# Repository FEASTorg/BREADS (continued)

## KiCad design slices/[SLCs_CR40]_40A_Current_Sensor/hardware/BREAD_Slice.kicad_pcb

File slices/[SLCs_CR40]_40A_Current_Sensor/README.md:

# Broadly Reconfigurable and Expandable Automation Device (BREAD) -- Slice Datasheet: 4**0A Current Sensor Slice** (SLC-CR40)

By: Nicholas Whisman (ngwhisma@mtu.edu) -- Revision 0, on

## Short Device Description

This slice acts as a current sensor, and is rated for up to ±40 Amps.
The sensor outputs a voltage signal linearly related to the current
flowing through the chip, at an approximate resolution of 50 mV / Amp.

## Quick Information

Device at a Glance

  --------------------- ---------------------------------
  Short title           40A Current Detector
  Part \#               SLC-CR40
  Repository Link       Link to OSF or other repository
  Academic Paper DOI    DOI link to published paper
  Device Cost           Monetary cost of the device
  Assembly Difficulty   Medium. Millable.
  Application Area      Power Analysis, Controls
  --------------------- ---------------------------------

Device Connections

Current Input Screw Terminals

  -------- -------------------------------------------------------------------------------------- --------
  Pin \#   Description                                                                            Rating
  J2       Sizeable blade connector for current channel throughput. Positive lead on the right.   50A+
  J3       Sizeable blade connector for current channel throughput. Positive lead on the right.   50A+
  J4       Sizeable blade connector for current channel throughput. Positive lead on the right.   50A+
  J5       Sizeable blade connector for current channel throughput. Positive lead on the right.   50A+
  J6       Sizeable blade connector for current channel throughput. Positive lead on the right.   50A+
  J7       Sizeable blade connector for current channel throughput. Positive lead on the right.   50A+
  J8       Sizeable blade connector for current channel throughput. Positive lead on the right.   50A+
  J9       Sizeable blade connector for current channel throughput. Positive lead on the right.   50A+
  -------- -------------------------------------------------------------------------------------- --------

## Commands

  --------------------------------------------------------------------- ------------ ------------------------ ----------------------------
  **Setup **(no significant returns)                                                                          
  **Byte**: Address                                                     **Bit**: 1   **Float: **Target Temp   **Float: **Ramp Rate (d/m)
  **Read Current **(returns the current through the selected channel)                                         
  **Byte**: Address                                                     **Bit**: 0   **Float: **0             **Float: **0
  --------------------------------------------------------------------- ------------ ------------------------ ----------------------------

## Schematic

![Figure 1: BREAD Connection Pins + Power
Capacitors](Pictures/10000201000000AB0000008BB51D58A998ECB56B.png "fig:"){width="1.7811in"
height="1.448in"}\
\
\
\
\
\
\
\
\
\
![Figure 2: Arduino
Nano](Pictures/10000201000000B4000000F5D2FAF377839CEBA3.png "fig:"){width="1.8752in"
height="2.552in"}\
\

![Figure 3: One of four identical current sensing
channels](Pictures/10000201000000F900000074C687B7F5A6EA3E1E.png "fig:"){width="2.5937in"
height="1.2083in"}

\
\
\
\
\
\

## Bill of Materials

  ------------ -------------------------------- ---------- ------------- -----------------------------------------------------------------------------------------------------------------------------------------------------------------
  Designator   Description                      Quantity   Cost / part   URL
  U1-4         40A Current Sensor Chip          4          5.68          <https://www.digikey.com/en/products/detail/allegro-microsystems/ACS723KMATR-40AB-T/5225380>
  J2-J9        Blade Connectors                 8          0.37          [https://www.digikey.com/en/products/detail/w%C3%BCrth-elektronik/7474966/9488016](https://www.digikey.com/en/products/detail/würth-elektronik/7474966/9488016)
  C1-2         1206 Packaging 10 µF Capacitor   2          0.64          <https://www.digikey.com/short/qfrbqfhd>
  A1           Arduino Nano                     1          22.00         <https://www.digikey.com/en/products/detail/arduino/A000005/2638989>
  J1           01x10 Female Header Pins         1          0.79          <https://www.digikey.com/short/23bfwwjh>
  ------------ -------------------------------- ---------- ------------- -----------------------------------------------------------------------------------------------------------------------------------------------------------------

## Construction & Fabrication

List any tools that are required and short guide on the order which
parts should be soldered / assembled. Be sure to note any specialized
methods and point out components that may easily be soldered in the
incorrect orientation. Additionally include at least one picture of the
assembled board (include both sides if there are components on both
sides).

\[Image of the assembled Circuit Board\]

Fig #. Subtitle should go here.

## Configuration & Calibration

Include a list of default jumper and potentiometer positions:

Hardware Positions

-   Turn P1 to be roughly 50%
-   Turn P2 to be completely closed (turn clockwise until potentiometer
    clicks)
-   Place a jumper to short out J3. Etc...

Detail any key parameters the end-user may want to adjust in the
firmware, and if there are any special instructions before programming
the Slice.

Tools Required For Calibration

-   An oscilloscope with at least 15Mhz sampling
-   A multimeter. Etc...

List all of the tools / instruments required for calibration. Provide a
detailed & step by step guide on how to calibrate (or validate) each
unique type of channel on the card. Include what variables in the
firmware may need to be adjusted (and when). Attach a wiring diagram for
each relevant calibration circuit.

\[Image of the calibration circuit\]

Fig #. Subtitle should go here.

## Usage & Constraints

List the relevant constraints for each type of channel on the card.
These parameters may be quantities like max current, max voltage,
frequency, sampling frequency, etc.

List an example wiring diagram of the slice in use, as well as some
suggested applications

\[Image of the example usage wiring diagram\]

Fig #. Subtitle should go here.

## General Comments on Slice

This section is intended as a catch-all for any topics that are relevant
to the Slice that don't fit in any other category.

## Revision Notes

-   Rev 0 -- Initial document release (DATE HERE)

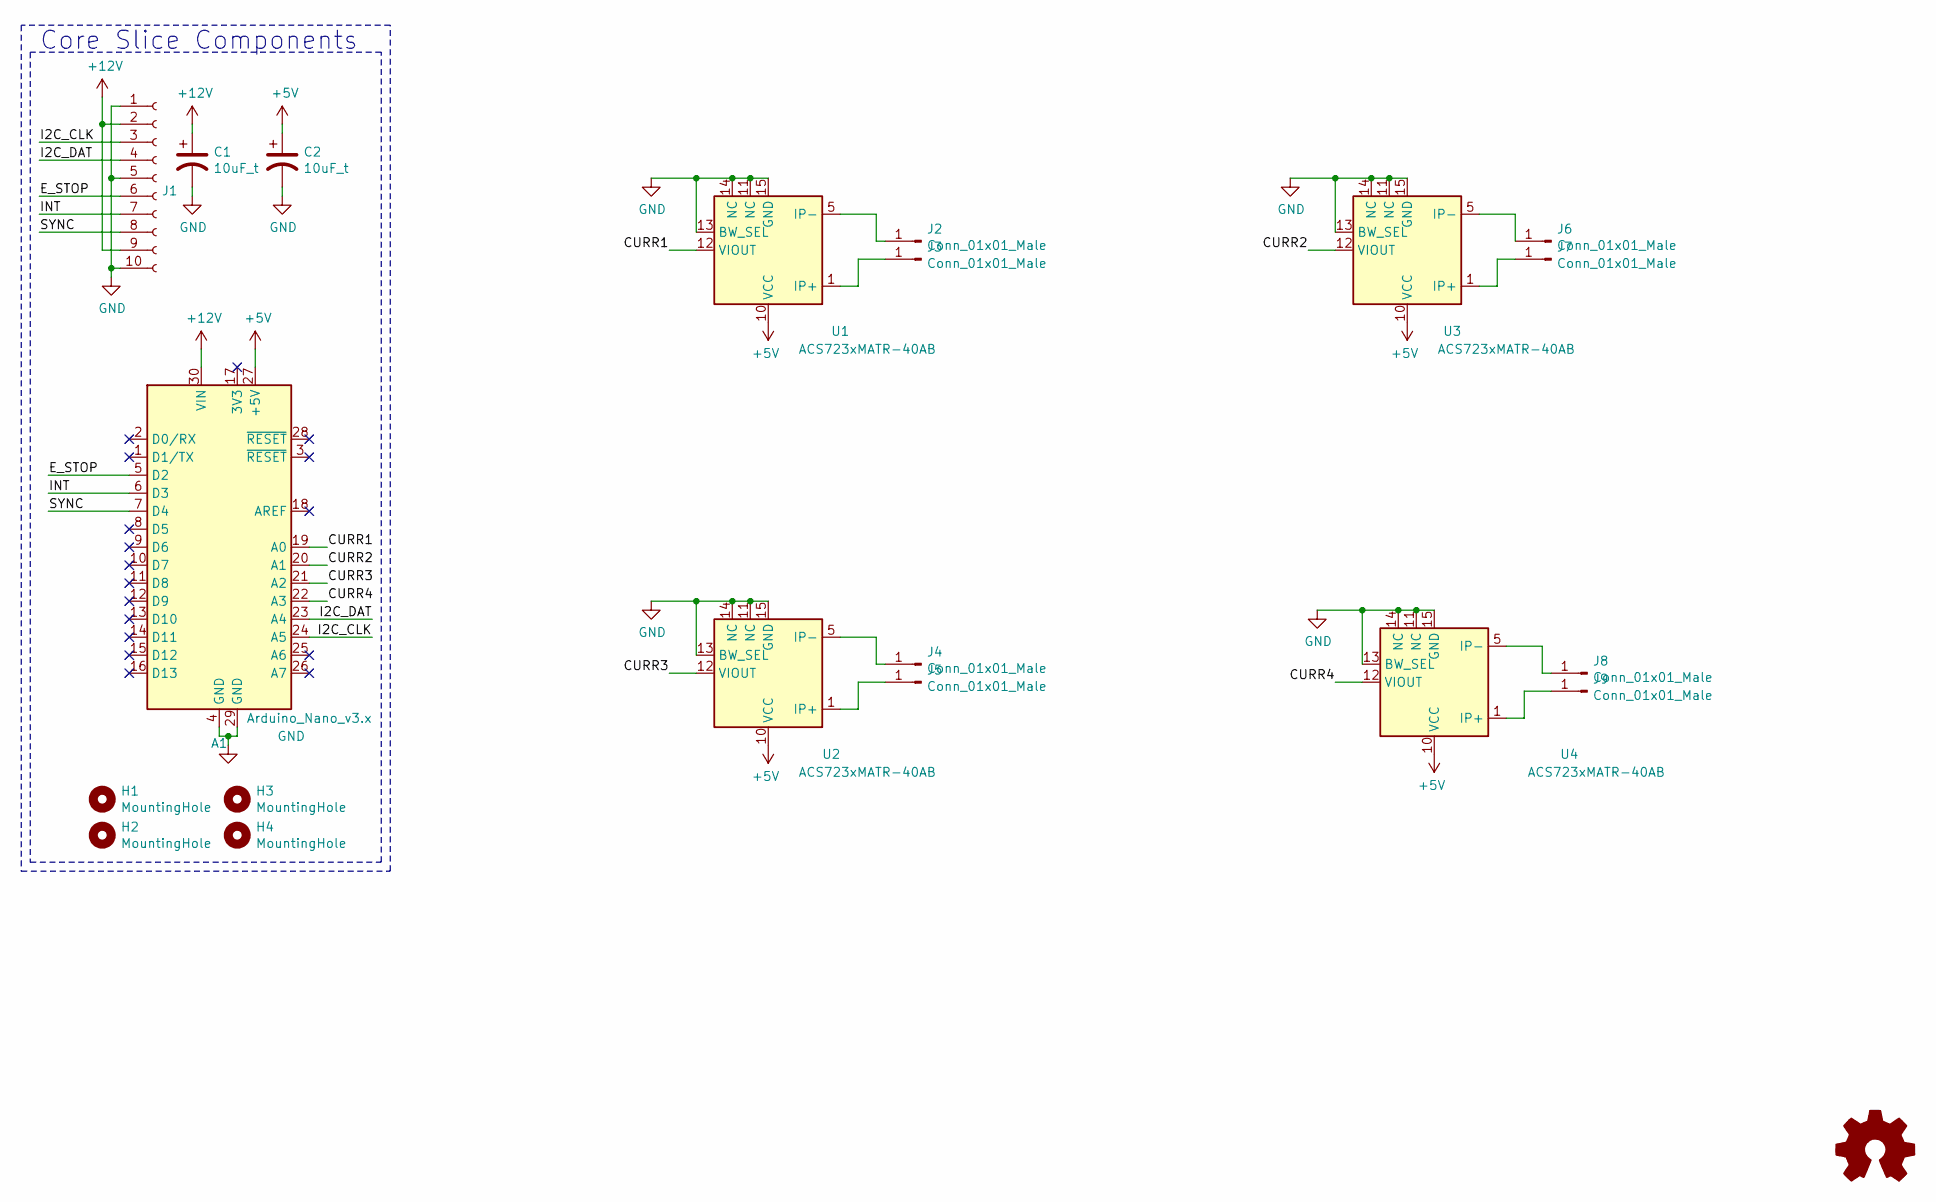
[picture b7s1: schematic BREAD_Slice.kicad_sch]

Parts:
A1: Arduino_Nano_v3.x; Arduino_Nano
C1, C2: 10uF_t; C_2312; Part # T491C106K025AT
H1, H2, H3, H4: MountingHole; MountingHole_3.2mm_M3_DIN965_Pad
J1: Conn_01x10_Female; PinSocket_1x10_P2.54mm_Horizontal
J2, J3, J4, J5, J6, J7, J8, J9: Conn_01x01_Male; Blade_Connector
Logo1: Logo_Open_Hardware_Small; OSHW-Symbol_6.7x6mm_SilkScreen
U1, U2, U3, U4: ACS723xMATR-40AB; SOIC-16W_7.5x10.3mm_P1.27mm

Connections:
+5V: A1.27 (+5V), C2.1, U1.10 (VCC), U2.10 (VCC), U3.10 (VCC), U4.10 (VCC)
+12V: A1.30 (VIN), C1.1, J1.2, J1.9
/CURR1: A1.19 (A0), U1.12 (VIOUT)
/CURR2: A1.20 (A1), U3.12 (VIOUT)
/CURR3: A1.21 (A2), U2.12 (VIOUT)
/CURR4: A1.22 (A3), U4.12 (VIOUT)
/E_STOP: A1.5 (D2), J1.6
/I2C_CLK: A1.24 (A5), J1.3
/I2C_DAT: A1.23 (A4), J1.4
/INT: A1.6 (D3), J1.7
/SYNC: A1.7 (D4), J1.8
GND: A1.4 (GND), A1.29 (GND), C1.2, C2.2, J1.1, J1.5, J1.10, U1.11 (NC), U1.13 (BW_SEL), U1.14 (NC), U1.15 (GND), U2.11 (NC), U2.13 (BW_SEL), U2.14 (NC), U2.15 (GND), U3.11 (NC), U3.13 (BW_SEL), U3.14 (NC), U3.15 (GND), U4.11 (NC), U4.13 (BW_SEL), U4.14 (NC), U4.15 (GND)
unnamed: J2.1, U1.5 (IP-), U1.6 (IP-), U1.7 (IP-), U1.8 (IP-)
unnamed: J3.1, U1.1 (IP+), U1.2 (IP+), U1.3 (IP+), U1.4 (IP+)
unnamed: J4.1, U2.5 (IP-), U2.6 (IP-), U2.7 (IP-), U2.8 (IP-)
unnamed: J5.1, U2.1 (IP+), U2.2 (IP+), U2.3 (IP+), U2.4 (IP+)
unnamed: J6.1, U3.5 (IP-), U3.6 (IP-), U3.7 (IP-), U3.8 (IP-)
unnamed: J7.1, U3.1 (IP+), U3.2 (IP+), U3.3 (IP+), U3.4 (IP+)
unnamed: J8.1, U4.5 (IP-), U4.6 (IP-), U4.7 (IP-), U4.8 (IP-)
unnamed: J9.1, U4.1 (IP+), U4.2 (IP+), U4.3 (IP+), U4.4 (IP+)

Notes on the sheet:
Core Slice Components

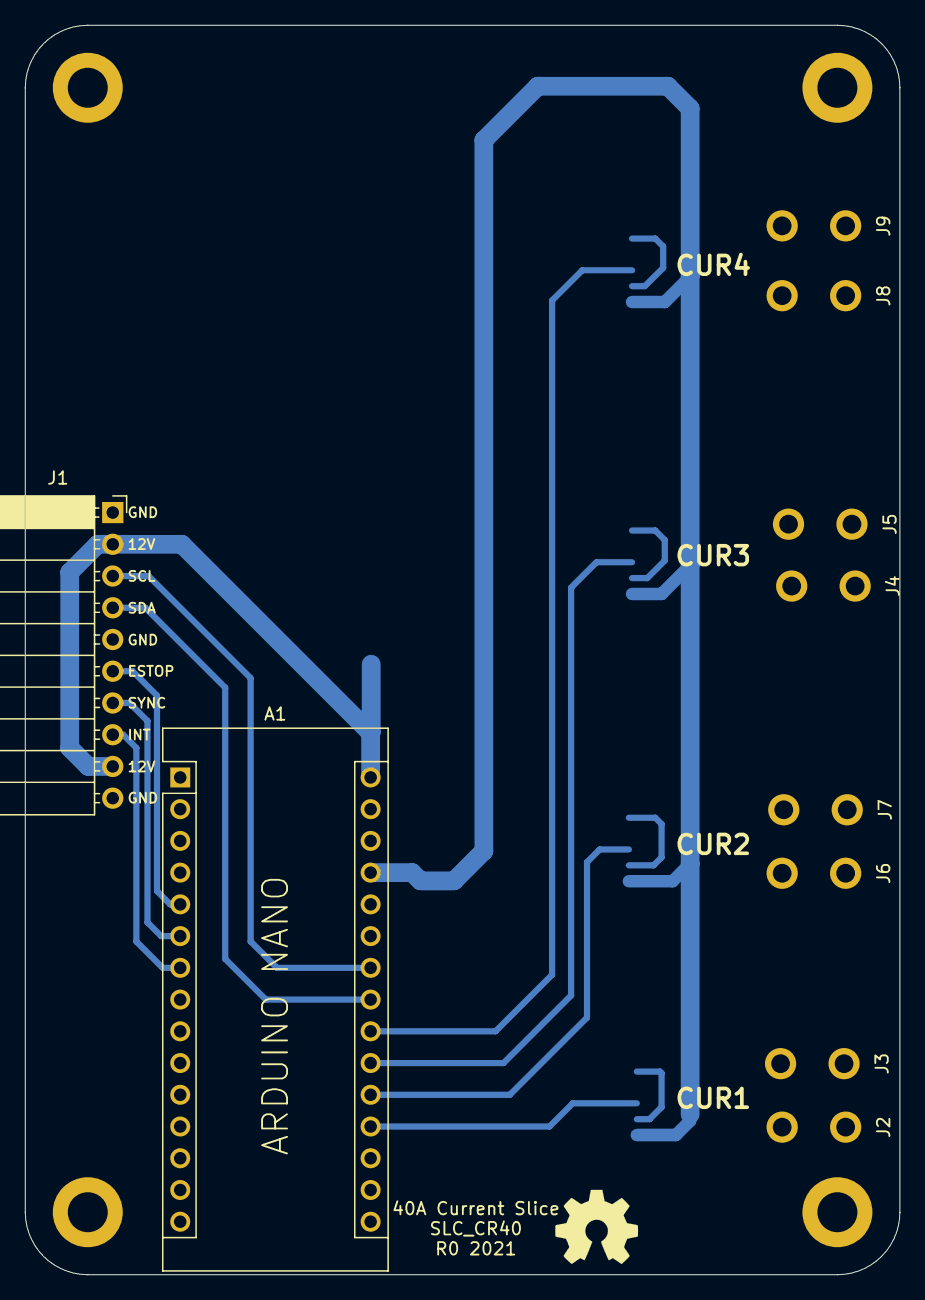
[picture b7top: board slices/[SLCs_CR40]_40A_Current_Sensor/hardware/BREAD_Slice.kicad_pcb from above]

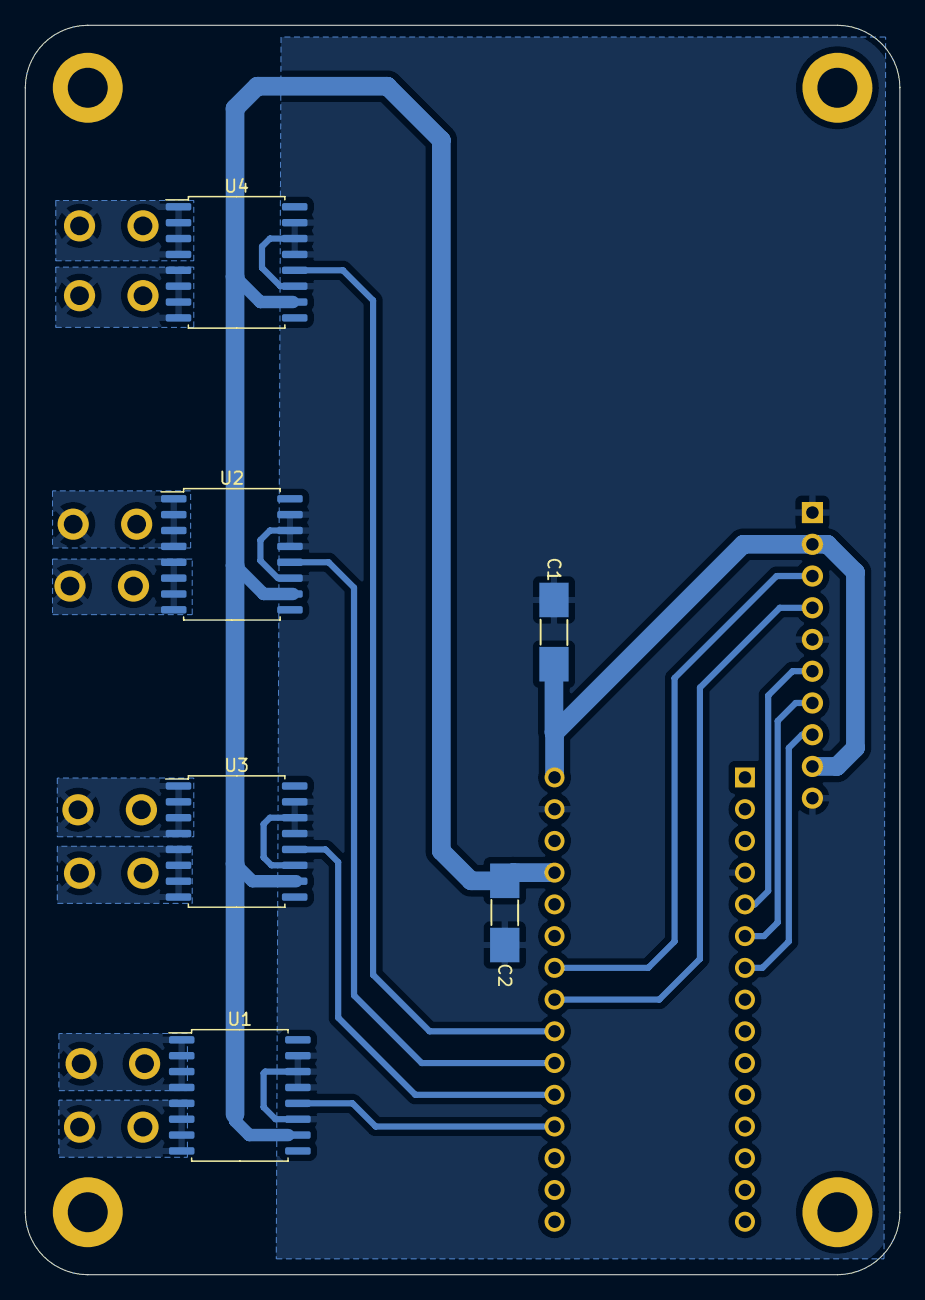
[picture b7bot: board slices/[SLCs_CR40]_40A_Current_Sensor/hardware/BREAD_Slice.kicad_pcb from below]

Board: 2 copper layers, 70.0 x 100.0 mm, 21 parts (6 on the bottom side), 20 nets.

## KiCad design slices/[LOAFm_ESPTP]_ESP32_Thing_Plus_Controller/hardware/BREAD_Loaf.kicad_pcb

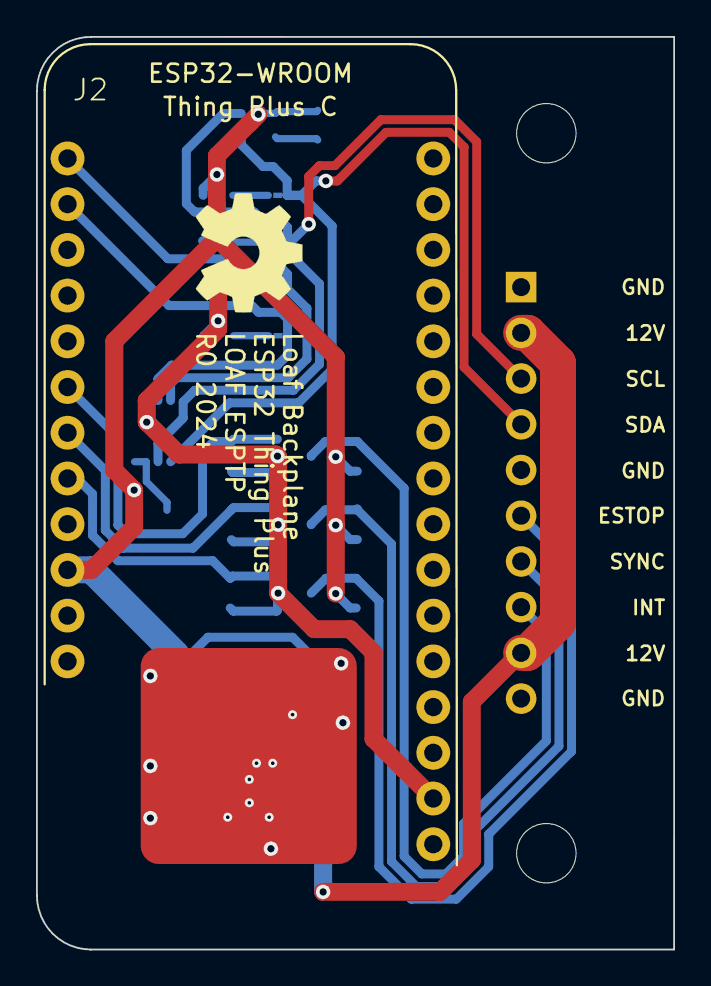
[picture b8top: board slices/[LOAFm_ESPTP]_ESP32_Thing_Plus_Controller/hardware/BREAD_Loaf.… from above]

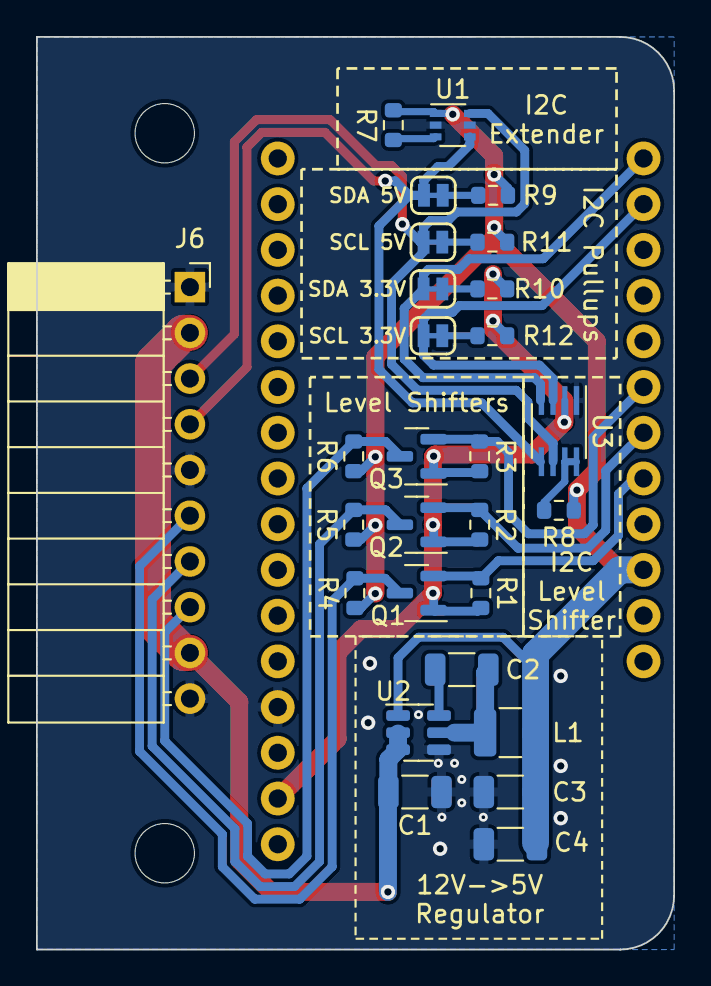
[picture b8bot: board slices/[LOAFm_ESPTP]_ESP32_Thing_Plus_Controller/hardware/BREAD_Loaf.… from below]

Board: 2 copper layers, 35.4 x 50.7 mm, 33 parts (28 on the bottom side), 22 nets.

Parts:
C1, C3, C4: 22uF; C_1206_3216Metric
C2: 100nF; C_1206_3216Metric
HS1: Heatsink_Pad; Thermal Pad
J2: THING_PLUS_LOGICAL; ESP_THING_PLUS
J6: PPPC101LGBN-RC; PinSocket_1x10_P2.54mm_Horizontal
JP1, JP2, JP3, JP4: SMT-JUMPER_2_NC_TRACE_SILK
L1: 4.7uH; L_1210_3225Metric
Logo1: Logo_Open_Hardware_Small; OSHW-Symbol_6.7x6mm_SilkScreen
Q1, Q2, Q3: BSS138; SOT-23
R1, R2, R3, R4, R5, R6, R7: 10k; R_0603_1608Metric
R8: 200k; R_0603_1608Metric
R9, R11: 4.7k; R_0603_1608Metric
R10, R12: 2.2k; R_0603_1608Metric
ST1, ST2: Stand_off; STAND-OFF
U1: LTC4311ISC6-TRMPBF; SOT-363_SC-70-6
U2: AP63205WU-7; TSOT-23-6
U3: PCA9306; SSOP-8_2.95x2.8mm_P0.65mm

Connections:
+3.3V: J2.27 (3.3V), Q1.1 (G), Q2.1 (G), Q3.1 (G), R1.2, R2.2, R3.2, R10.1, R12.1, U3.2 (VREF1)
+5V: C3.2, C4.2, J2.10 (V_USB), L1.2, R4.2, R5.2, R6.2, R7.1, R8.2, R9.1, R11.1, U1.1 (VCC), U2.1 (FB)
+12V: C1.2, J6.2, J6.9, U2.2 (EN), U2.3 (VIN)
/E_STOP_3.3V: J2.8 (GPIO1), Q1.2 (S), R1.1
/E_STOP_5V: J6.6, Q1.3 (D), R4.1
/INT_3.3V: J2.7 (GPIO2), Q2.2 (S), R2.1
/INT_5V: J6.7, Q2.3 (D), R5.1
/SCL_3.3V: J2.2 (SCL), JP4.2 (B), U3.3 (SCL1)
/SCL_5V: J6.3, JP2.2 (B), U1.6 (BUS1), U3.6 (SCL2)
/SDA_3.3V: J2.1 (SDA), JP3.2 (B), U3.4 (SDA1)
/SDA_5V: J6.4, JP1.2 (B), U1.4 (BUS2), U3.5 (SDA2)
/SYNC_3.3V: J2.6 (GPIO3), Q3.2 (S), R3.1
/SYNC_5V: J6.8, Q3.3 (D), R6.1
GND: C1.1, C3.1, C4.1, HS1.1, J2.25 (GND), J6.1, J6.5, J6.10, U1.2 (GND), U1.5 (GND), U2.4 (GND), U3.1 (GND)
unnamed: JP1.1 (A), R9.2
unnamed: JP2.1 (A), R11.2
unnamed: JP3.1 (A), R10.2
unnamed: JP4.1 (A), R12.2
unnamed: R7.2, U1.3 (ENABLE)
unnamed: C2.2, U2.6 (BST)
unnamed: C2.1, L1.1, U2.5 (SW)
unnamed: R8.1, U3.7 (VREF2), U3.8 (EN)

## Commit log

2024-04-18 Organizing
2024-04-18 Update README.md links
2024-04-21 removed old LOAF
2024-04-21 Lots of refactoring and organizing
2024-04-21 updated READMEs
2024-04-22 restructuring for rpi boards
2024-05-12 Initial commit of discrete hbridge motor driver
2024-05-18 first pass of ph do ec rp slice
2024-05-19 improved phdo and initial ERC pass on PDER
2024-05-20 Initial Sparkfun conversion to BREAD and ERC check hier
2024-05-20 added template folder placeholder files
2024-05-21 atlas oem slice footprints all done and at routing stage
2024-05-22 Initial commit and ERC pass for HPTC
2024-05-22 updated README with new PCBs
2024-05-23 splitting of repos
2024-05-24 added script for dev usage (pull all repos)
2024-07-23 added BREAD logo by emily
2024-08-30 updated tables and added some future bread info
2024-09-09 local push
2024-09-10 updated tracker
2024-09-10 organization of core docs
2024-09-10 corrected bread core images
2024-09-10 updated slice repos and tables
2024-09-10 updated general and release status tracker
2024-09-11 added colour chart for silkscreen colours
2024-09-11 added tools docs for kicad development
2024-09-13 updated tracker with latest updates
2025-04-01 updated tracker and production guidelines
2025-04-17 updated docs and tracker
2025-04-18 updated docs
2025-04-19 updated progress tracker
2025-04-19 updated slice ideas docs
2025-04-20 added echm idea and moved general ee info docs to kneead
2025-04-20 updated future ideas
2025-04-20 did some updatets to align with FEAST main repo
2025-04-22 added notes to progress on each slice
2025-04-25 added artifacts for pages
2025-04-25 added auto indexing of docs
2025-04-25 fixed comma in py ext...turns out it can run locally like that?
2025-04-25 regenerate index pages
2025-04-25 small change to trigger
2025-04-25 🔁 Auto-generate docs indexes
2025-04-25 updated summaries
2025-04-25 updated wf
2025-04-25 updated docs readme
2025-04-25 🔁 Auto-generate docs index and sync ignores
2025-04-25 update to BREADS
2025-04-26 moved config to docs/
2025-04-26 added todo.md to exclude in yml
2025-04-26 updated index
2025-05-02 minor updates to docs
2025-05-04 update orders sequence
2025-05-05 updated progress
2025-09-07 clean repo before pulling into main site
2025-09-07 move: branding->docs/assets
2025-09-07 remove old pages artifacts
2025-09-07 add .indexignore
2025-09-07 change title of index
2025-09-07 minor: update readme and indexignore
2025-09-07 remove old link from readme
2025-09-07 update to new link
2025-09-08 add README to indexignore
2025-09-08 remove old generated contents in favour of auto toc
2025-09-08 docs: restructure
2025-09-23 docs: move around and rename docs; overall revise and move to other repos where appropriate
2025-09-28 update and move future ideas
2026-01-22 update history
2026-01-22 minor revisions
2026-01-26 transfer SLICE docs
2026-01-27 add loaf stuff from repo
2026-01-31 update hardware summary front license
2026-01-31 change informative front license to md for viewing
2026-02-04 add list of boards to update lib
2026-02-04 add tag line
2026-02-10 update progress
2026-04-20 refactor: org casing rename from 'FEASTorg' to 'feastorg'
2026-05-01 docs: revise, update, and restructure the slice materials
